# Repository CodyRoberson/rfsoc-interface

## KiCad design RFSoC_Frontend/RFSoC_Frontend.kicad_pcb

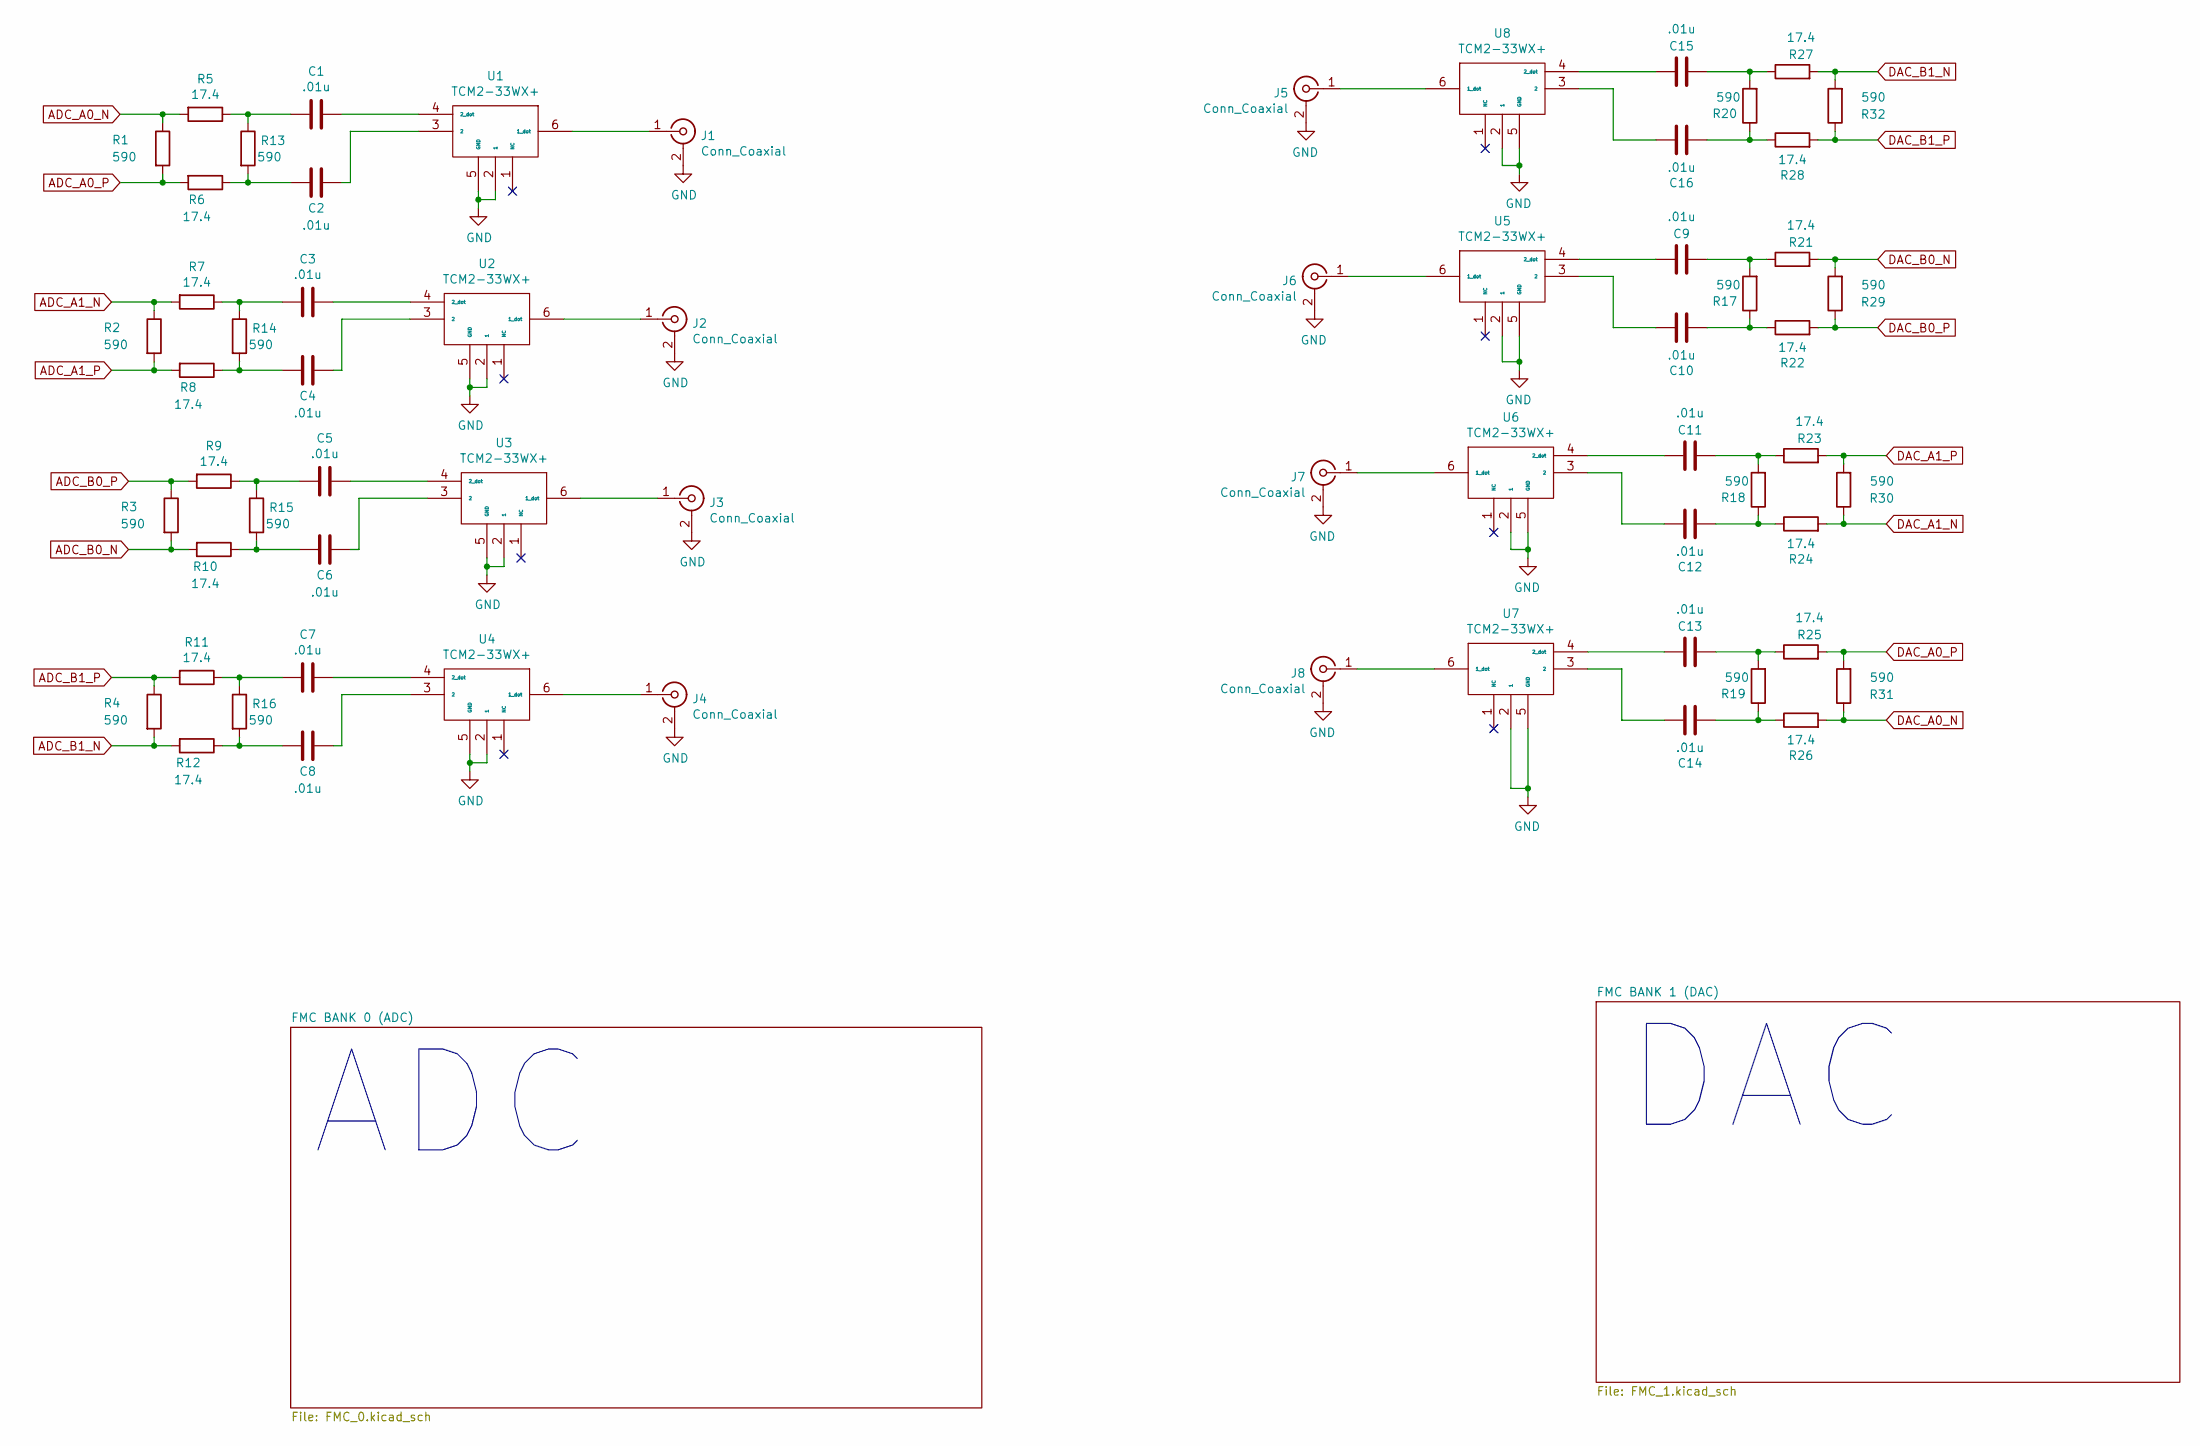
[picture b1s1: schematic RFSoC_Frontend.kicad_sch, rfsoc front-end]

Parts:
C1, C2, C3, C4, C5, C6, C7, C8, C9, C10, C11, C12, C13, C14, C15, C16: .01u; C_0402_1005Metric; Mouser Part Number 963-LMF105B7103KVHF
J1, J2, J3, J4, J5, J6, J7, J8: Conn_Coaxial; SMA_Amphenol_132289_EdgeMount
R1, R2, R3, R4, R13, R14, R15, R16, R17, R18, R19, R20, R29, R30, R31, R32: 590; R_0402_1005Metric; Mouser Part Number 667-ERA-2AEB5900X
R5, R6, R7, R8, R9, R10, R11, R12, R21, R22, R23, R24, R25, R26, R27, R28: 17.4; R_0402_1005Metric; Mouser Part Number 71-CRCW0402-17.4-E3
U1, U2, U3, U4, U5, U6, U7, U8: TCM2-33WX+; XFMR_TCM2-33WX+; Mouser Part Number 139-TCM2-33WX

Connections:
ADC_A0_N: R1.1, R5.2; also elsewhere on the board
ADC_A0_P: R1.2, R6.2; also elsewhere on the board
ADC_A1_N: R2.1, R7.2; also elsewhere on the board
ADC_A1_P: R2.2, R8.2; also elsewhere on the board
ADC_B0_N: R3.2, R10.2; also elsewhere on the board
ADC_B0_P: R3.1, R9.2; also elsewhere on the board
ADC_B1_N: R4.2, R12.2; also elsewhere on the board
ADC_B1_P: R4.1, R11.2; also elsewhere on the board
DAC_A0_N: R26.2, R31.1; also elsewhere on the board
DAC_A0_P: R25.2, R31.2; also elsewhere on the board
DAC_A1_N: R24.2, R30.1; also elsewhere on the board
DAC_A1_P: R23.2, R30.2; also elsewhere on the board
DAC_B0_N: R21.2, R29.2; also elsewhere on the board
DAC_B0_P: R22.2, R29.1; also elsewhere on the board
DAC_B1_N: R27.2, R32.2; also elsewhere on the board
DAC_B1_P: R28.2, R32.1; also elsewhere on the board
GND: J1.2 (Ext), J2.2 (Ext), J3.2 (Ext), J4.2 (Ext), J5.2 (Ext), J6.2 (Ext), J7.2 (Ext), J8.2 (Ext), U1.2 (1), U1.5 (GND), U2.2 (1), U2.5 (GND), U3.2 (1), U3.5 (GND), U4.2 (1), U4.5 (GND), U5.2 (1), U5.5 (GND), U6.2 (1), U6.5 (GND), U7.2 (1), U7.5 (GND), U8.2 (1), U8.5 (GND); also elsewhere on the board
unnamed: C1.1, U1.4 (2_dot)
unnamed: C1.2, R5.1, R13.1
unnamed: C2.1, U1.3 (2)
unnamed: C2.2, R6.1, R13.2
unnamed: C3.1, U2.4 (2_dot)
unnamed: C3.2, R7.1, R14.1
unnamed: C4.1, U2.3 (2)
unnamed: C4.2, R8.1, R14.2
unnamed: C5.1, U3.4 (2_dot)
unnamed: C5.2, R9.1, R15.1
unnamed: C6.1, U3.3 (2)
unnamed: C6.2, R10.1, R15.2
unnamed: C7.1, U4.4 (2_dot)
unnamed: C7.2, R11.1, R16.1
unnamed: C8.1, U4.3 (2)
unnamed: C8.2, R12.1, R16.2
unnamed: C9.1, U5.4 (2_dot)
unnamed: C9.2, R17.2, R21.1
unnamed: C10.1, U5.3 (2)
unnamed: C10.2, R17.1, R22.1
unnamed: C11.1, U6.4 (2_dot)
unnamed: C11.2, R18.2, R23.1
unnamed: C12.1, U6.3 (2)
unnamed: C12.2, R18.1, R24.1
unnamed: C13.1, U7.4 (2_dot)
unnamed: C13.2, R19.2, R25.1
unnamed: C14.1, U7.3 (2)
unnamed: C14.2, R19.1, R26.1
unnamed: C15.1, U8.4 (2_dot)
unnamed: C15.2, R20.2, R27.1
unnamed: C16.1, U8.3 (2)
unnamed: C16.2, R20.1, R28.1
unnamed: J1.1 (In), U1.6 (1_dot)
unnamed: J2.1 (In), U2.6 (1_dot)
unnamed: J3.1 (In), U3.6 (1_dot)
unnamed: J4.1 (In), U4.6 (1_dot)
unnamed: J5.1 (In), U8.6 (1_dot)
unnamed: J6.1 (In), U5.6 (1_dot)
unnamed: J7.1 (In), U6.6 (1_dot)
unnamed: J8.1 (In), U7.6 (1_dot)

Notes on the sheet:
ADC
DAC

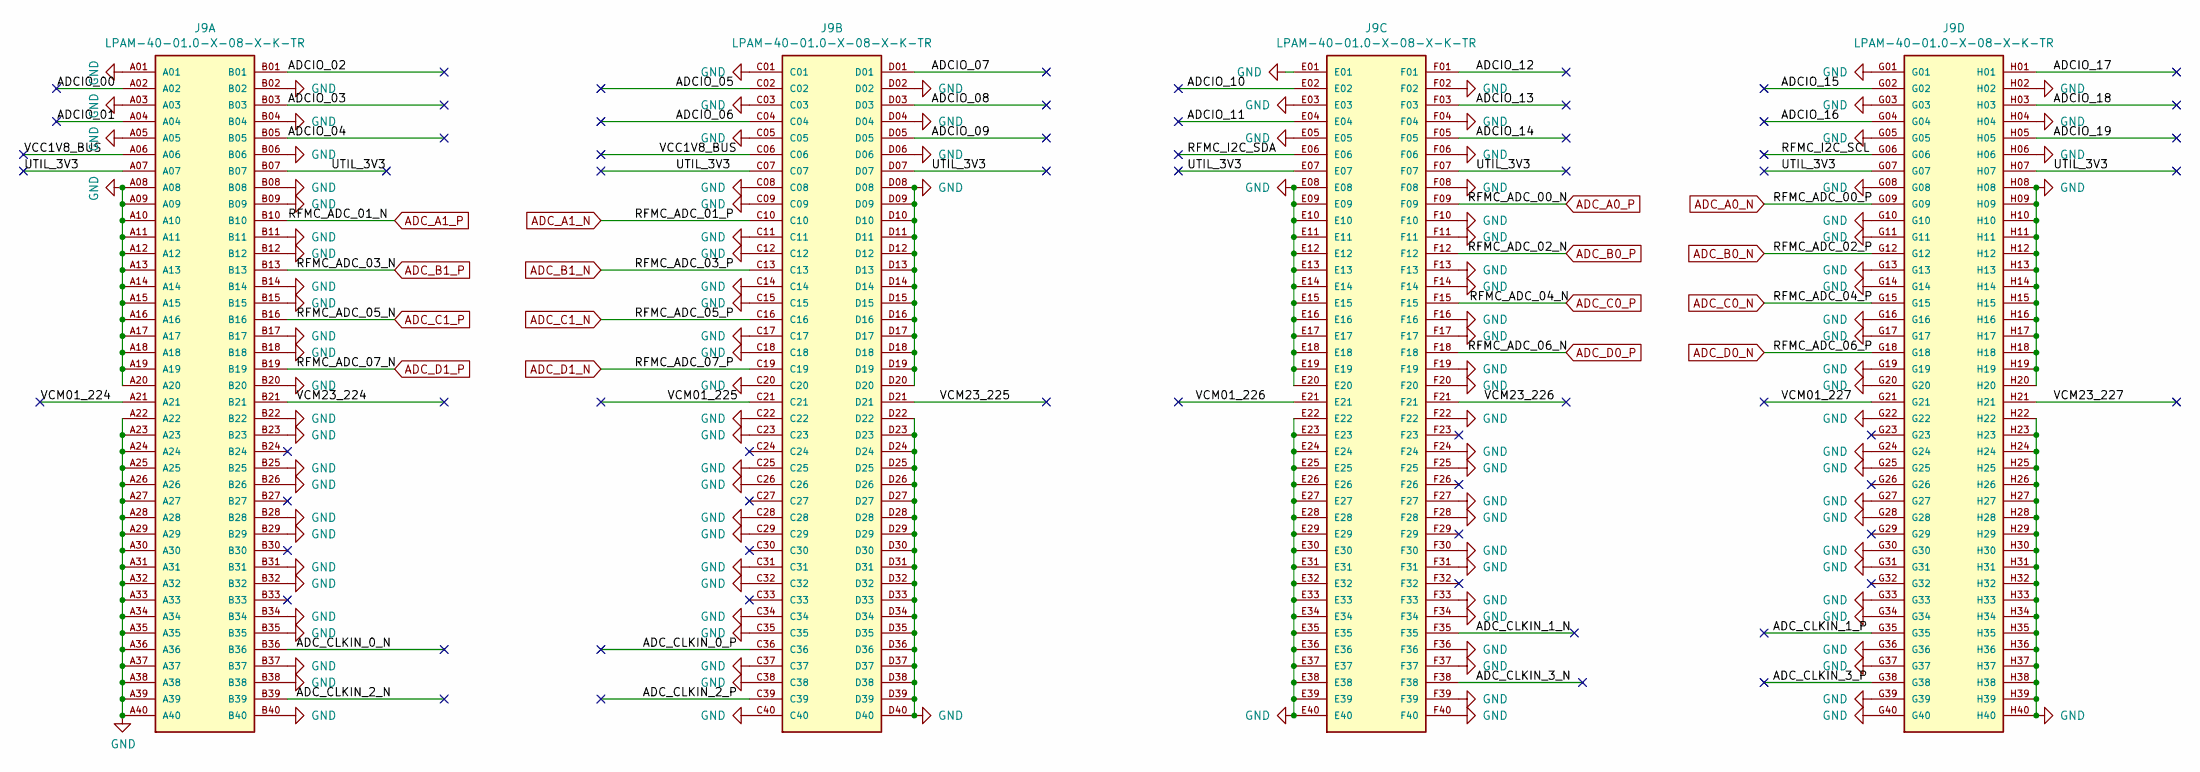
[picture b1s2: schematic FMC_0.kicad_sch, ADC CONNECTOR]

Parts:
J9: LPAM-40-01.0-X-08-X-K-TR; SAMTEC_LPAM-40-01.0-X-08-X-K-TR; PARTREV E

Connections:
/FMC BANK 0 (ADC)/ADCIO_00: J9.A02
/FMC BANK 0 (ADC)/ADCIO_01: J9.A04
/FMC BANK 0 (ADC)/ADCIO_02: J9.B01
/FMC BANK 0 (ADC)/ADCIO_03: J9.B03
/FMC BANK 0 (ADC)/ADCIO_04: J9.B05
/FMC BANK 0 (ADC)/ADCIO_05: J9.C02
/FMC BANK 0 (ADC)/ADCIO_06: J9.C04
/FMC BANK 0 (ADC)/ADCIO_07: J9.D01
/FMC BANK 0 (ADC)/ADCIO_08: J9.D03
/FMC BANK 0 (ADC)/ADCIO_09: J9.D05
/FMC BANK 0 (ADC)/ADCIO_10: J9.E02
/FMC BANK 0 (ADC)/ADCIO_11: J9.E04
/FMC BANK 0 (ADC)/ADCIO_12: J9.F01
/FMC BANK 0 (ADC)/ADCIO_13: J9.F03
/FMC BANK 0 (ADC)/ADCIO_14: J9.F05
/FMC BANK 0 (ADC)/ADCIO_15: J9.G02
/FMC BANK 0 (ADC)/ADCIO_16: J9.G04
/FMC BANK 0 (ADC)/ADCIO_17: J9.H01
/FMC BANK 0 (ADC)/ADCIO_18: J9.H03
/FMC BANK 0 (ADC)/ADCIO_19: J9.H05
/FMC BANK 0 (ADC)/ADC_CLKIN_0_N: J9.B36
/FMC BANK 0 (ADC)/ADC_CLKIN_0_P: J9.C36
/FMC BANK 0 (ADC)/ADC_CLKIN_1_N: J9.F35
/FMC BANK 0 (ADC)/ADC_CLKIN_1_P: J9.G35
/FMC BANK 0 (ADC)/ADC_CLKIN_2_N: J9.B39
/FMC BANK 0 (ADC)/ADC_CLKIN_2_P: J9.C39
/FMC BANK 0 (ADC)/ADC_CLKIN_3_N: J9.F38
/FMC BANK 0 (ADC)/ADC_CLKIN_3_P: J9.G38
/FMC BANK 0 (ADC)/RFMC_I2C_SCL: J9.G06
/FMC BANK 0 (ADC)/RFMC_I2C_SDA: J9.E06
/FMC BANK 0 (ADC)/UTIL_3V3: J9.A07, J9.B07, J9.C07, J9.D07, J9.E07, J9.F07, J9.G07, J9.H07
/FMC BANK 0 (ADC)/VCC1V8_BUS: J9.A06, J9.C06
/FMC BANK 0 (ADC)/VCM01_224: J9.A21
/FMC BANK 0 (ADC)/VCM01_225: J9.C21
/FMC BANK 0 (ADC)/VCM01_226: J9.E21
/FMC BANK 0 (ADC)/VCM01_227: J9.G21
/FMC BANK 0 (ADC)/VCM23_224: J9.B21
/FMC BANK 0 (ADC)/VCM23_225: J9.D21
/FMC BANK 0 (ADC)/VCM23_226: J9.F21
/FMC BANK 0 (ADC)/VCM23_227: J9.H21
ADC_A0_N: J9.G09; also elsewhere on the board
ADC_A0_P: J9.F09; also elsewhere on the board
ADC_A1_N: J9.C10; also elsewhere on the board
ADC_A1_P: J9.B10; also elsewhere on the board
ADC_B0_N: J9.G12; also elsewhere on the board
ADC_B0_P: J9.F12; also elsewhere on the board
ADC_B1_N: J9.C13; also elsewhere on the board
ADC_B1_P: J9.B13; also elsewhere on the board
ADC_C0_N: J9.G15
ADC_C0_P: J9.F15
ADC_C1_N: J9.C16
ADC_C1_P: J9.B16
ADC_D0_N: J9.G18
ADC_D0_P: J9.F18
ADC_D1_N: J9.C19
ADC_D1_P: J9.B19
GND: J9.A01, J9.A03, J9.A05, J9.A08, J9.A09, J9.A10, J9.A11, J9.A12, J9.A13, J9.A14, J9.A15, J9.A16, J9.A17, J9.A18, J9.A19, J9.A20, J9.A22, J9.A23, J9.A24, J9.A25, J9.A26, J9.A27, J9.A28, J9.A29, J9.A30, J9.A31, J9.A32, J9.A33, J9.A34, J9.A35, J9.A36, J9.A37, J9.A38, J9.A39, J9.A40, J9.B02, J9.B04, J9.B06, J9.B08, J9.B09, J9.B11, J9.B12, J9.B14, J9.B15, J9.B17, J9.B18, J9.B20, J9.B22, J9.B23, J9.B25, J9.B26, J9.B28, J9.B29, J9.B31, J9.B32, J9.B34, J9.B35, J9.B37, J9.B38, J9.B40, J9.C01, J9.C03, J9.C05, J9.C08, J9.C09, J9.C11, J9.C12, J9.C14, J9.C15, J9.C17, J9.C18, J9.C20, J9.C22, J9.C23, J9.C25, J9.C26, J9.C28, J9.C29, J9.C31, J9.C32, J9.C34, J9.C35, J9.C37, J9.C38, J9.C40, J9.D02, J9.D04, J9.D06, J9.D08, J9.D09, J9.D10, J9.D11, J9.D12, J9.D13, J9.D14, J9.D15, J9.D16, J9.D17, J9.D18, J9.D19, J9.D20, J9.D22, J9.D23, J9.D24, J9.D25, J9.D26, J9.D27, J9.D28, J9.D29, J9.D30, J9.D31, J9.D32, J9.D33, J9.D34, J9.D35, J9.D36, J9.D37, J9.D38, J9.D39, J9.D40, J9.E01, J9.E03, J9.E05, J9.E08, J9.E09, J9.E10, J9.E11, J9.E12, J9.E13, J9.E14, J9.E15, J9.E16, J9.E17, J9.E18, J9.E19, J9.E20, J9.E22, J9.E23, J9.E24, J9.E25, J9.E26, J9.E27, J9.E28, J9.E29, J9.E30, J9.E31, J9.E32, J9.E33, J9.E34, J9.E35, J9.E36, J9.E37, J9.E38, J9.E39, J9.E40, J9.F02, J9.F04, J9.F06, J9.F08, J9.F10, J9.F11, J9.F13, J9.F14, J9.F16, J9.F17, J9.F19, J9.F20, J9.F22, J9.F24, J9.F25, J9.F27, J9.F28, J9.F30, J9.F31, J9.F33, J9.F34, J9.F36, J9.F37, J9.F39, J9.F40, J9.G01, J9.G03, J9.G05, J9.G08, J9.G10, J9.G11, J9.G13, J9.G14, J9.G16, J9.G17, J9.G19, J9.G20, J9.G22, J9.G24, J9.G25, J9.G27, J9.G28, J9.G30, J9.G31, J9.G33, J9.G34, J9.G36, J9.G37, J9.G39, J9.G40, J9.H02, J9.H04, J9.H06, J9.H08, J9.H09, J9.H10, J9.H11, J9.H12, J9.H13, J9.H14, J9.H15, J9.H16, J9.H17, J9.H18, J9.H19, J9.H20, J9.H22, J9.H23, J9.H24, J9.H25, J9.H26, J9.H27, J9.H28, J9.H29, J9.H30, J9.H31, J9.H32, J9.H33, J9.H34, J9.H35, J9.H36, J9.H37, J9.H38, J9.H39, J9.H40; also elsewhere on the board

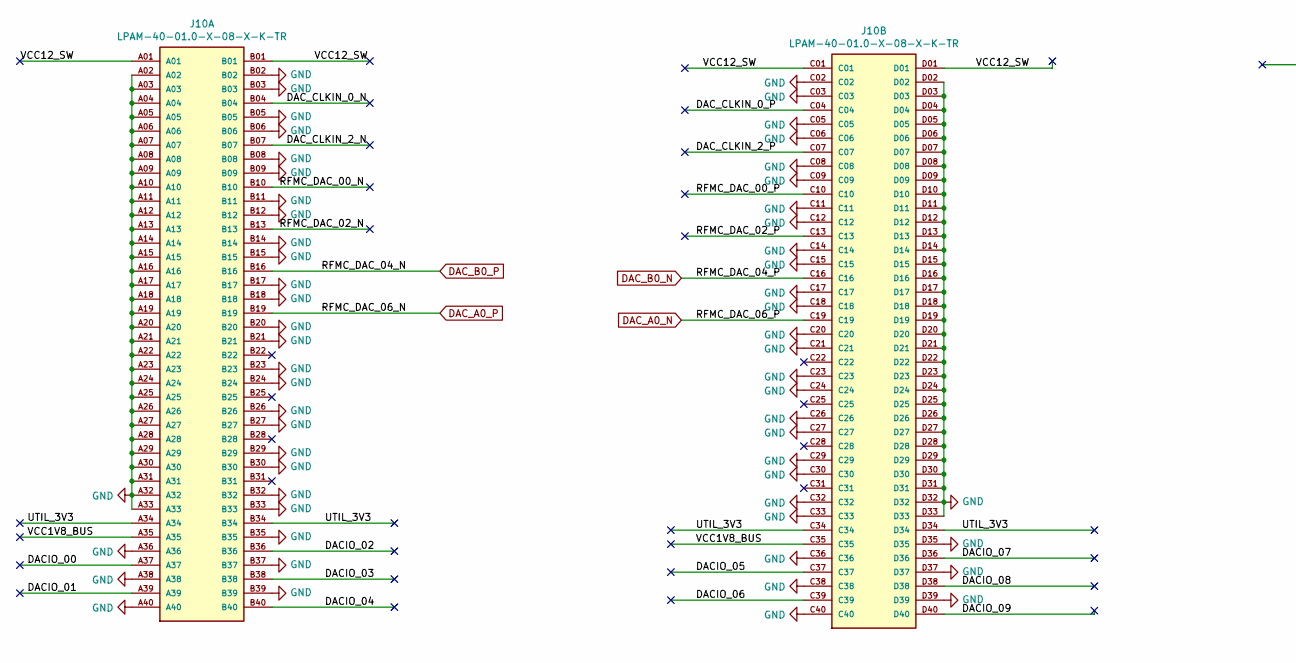
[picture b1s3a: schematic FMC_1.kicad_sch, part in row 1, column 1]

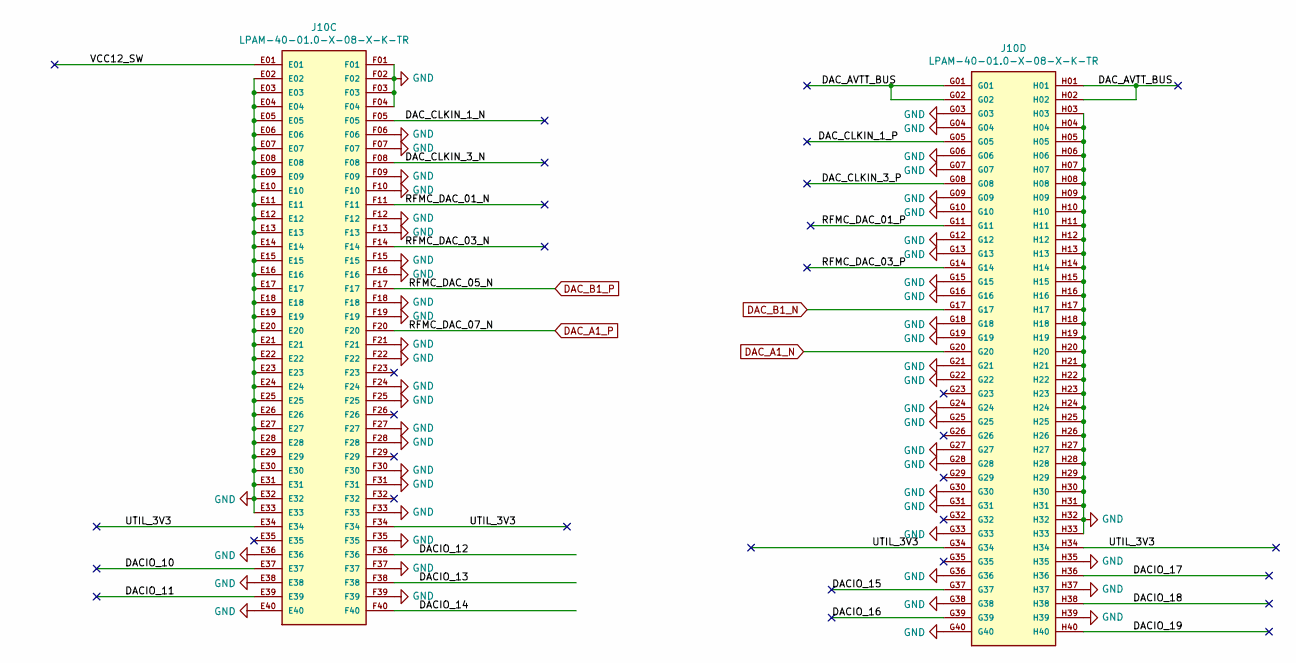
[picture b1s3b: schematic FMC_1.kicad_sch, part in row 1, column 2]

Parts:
J10: LPAM-40-01.0-X-08-X-K-TR; SAMTEC_LPAM-40-01.0-X-08-X-K-TR; PARTREV E

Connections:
/FMC BANK 1 (DAC)/DACIO_00: J10.A37
/FMC BANK 1 (DAC)/DACIO_01: J10.A39
/FMC BANK 1 (DAC)/DACIO_02: J10.B36
/FMC BANK 1 (DAC)/DACIO_03: J10.B38
/FMC BANK 1 (DAC)/DACIO_04: J10.B40
/FMC BANK 1 (DAC)/DACIO_05: J10.C37
/FMC BANK 1 (DAC)/DACIO_06: J10.C39
/FMC BANK 1 (DAC)/DACIO_07: J10.D36
/FMC BANK 1 (DAC)/DACIO_08: J10.D38
/FMC BANK 1 (DAC)/DACIO_09: J10.D40
/FMC BANK 1 (DAC)/DACIO_10: J10.E37
/FMC BANK 1 (DAC)/DACIO_11: J10.E39
/FMC BANK 1 (DAC)/DACIO_12: J10.F36
/FMC BANK 1 (DAC)/DACIO_13: J10.F38
/FMC BANK 1 (DAC)/DACIO_14: J10.F40
/FMC BANK 1 (DAC)/DACIO_15: J10.G37
/FMC BANK 1 (DAC)/DACIO_16: J10.G39
/FMC BANK 1 (DAC)/DACIO_17: J10.H36
/FMC BANK 1 (DAC)/DACIO_18: J10.H38
/FMC BANK 1 (DAC)/DACIO_19: J10.H40
/FMC BANK 1 (DAC)/DAC_AVTT_BUS: J10.G01, J10.G02, J10.H01, J10.H02
/FMC BANK 1 (DAC)/DAC_CLKIN_0_N: J10.B04
/FMC BANK 1 (DAC)/DAC_CLKIN_0_P: J10.C04
/FMC BANK 1 (DAC)/DAC_CLKIN_1_N: J10.F05
/FMC BANK 1 (DAC)/DAC_CLKIN_1_P: J10.G05
/FMC BANK 1 (DAC)/DAC_CLKIN_2_N: J10.B07
/FMC BANK 1 (DAC)/DAC_CLKIN_2_P: J10.C07
/FMC BANK 1 (DAC)/DAC_CLKIN_3_N: J10.F08
/FMC BANK 1 (DAC)/DAC_CLKIN_3_P: J10.G08
/FMC BANK 1 (DAC)/RFMC_DAC_00_N: J10.B10
/FMC BANK 1 (DAC)/RFMC_DAC_00_P: J10.C10
/FMC BANK 1 (DAC)/RFMC_DAC_01_N: J10.F11
/FMC BANK 1 (DAC)/RFMC_DAC_01_P: J10.G11
/FMC BANK 1 (DAC)/RFMC_DAC_02_N: J10.B13
/FMC BANK 1 (DAC)/RFMC_DAC_02_P: J10.C13
/FMC BANK 1 (DAC)/RFMC_DAC_03_N: J10.F14
/FMC BANK 1 (DAC)/RFMC_DAC_03_P: J10.G14
/FMC BANK 1 (DAC)/UTIL_3V3: J10.A34, J10.B34, J10.C34, J10.D34, J10.E34, J10.F34, J10.G34, J10.H34
/FMC BANK 1 (DAC)/VCC1V8_BUS: J10.A35, J10.C35
/FMC BANK 1 (DAC)/VCC12_SW: J10.A01, J10.B01, J10.C01, J10.D01, J10.E01
DAC_A0_N: J10.C19; also elsewhere on the board
DAC_A0_P: J10.B19; also elsewhere on the board
DAC_A1_N: J10.G20; also elsewhere on the board
DAC_A1_P: J10.F20; also elsewhere on the board
DAC_B0_N: J10.C16; also elsewhere on the board
DAC_B0_P: J10.B16; also elsewhere on the board
DAC_B1_N: J10.G17; also elsewhere on the board
DAC_B1_P: J10.F17; also elsewhere on the board
GND: J10.A02, J10.A03, J10.A04, J10.A05, J10.A06, J10.A07, J10.A08, J10.A09, J10.A10, J10.A11, J10.A12, J10.A13, J10.A14, J10.A15, J10.A16, J10.A17, J10.A18, J10.A19, J10.A20, J10.A21, J10.A22, J10.A23, J10.A24, J10.A25, J10.A26, J10.A27, J10.A28, J10.A29, J10.A30, J10.A31, J10.A32, J10.A33, J10.A36, J10.A38, J10.A40, J10.B02, J10.B03, J10.B05, J10.B06, J10.B08, J10.B09, J10.B11, J10.B12, J10.B14, J10.B15, J10.B17, J10.B18, J10.B20, J10.B21, J10.B23, J10.B24, J10.B26, J10.B27, J10.B29, J10.B30, J10.B32, J10.B33, J10.B35, J10.B37, J10.B39, J10.C02, J10.C03, J10.C05, J10.C06, J10.C08, J10.C09, J10.C11, J10.C12, J10.C14, J10.C15, J10.C17, J10.C18, J10.C20, J10.C21, J10.C23, J10.C24, J10.C26, J10.C27, J10.C29, J10.C30, J10.C32, J10.C33, J10.C36, J10.C38, J10.C40, J10.D02, J10.D03, J10.D04, J10.D05, J10.D06, J10.D07, J10.D08, J10.D09, J10.D10, J10.D11, J10.D12, J10.D13, J10.D14, J10.D15, J10.D16, J10.D17, J10.D18, J10.D19, J10.D20, J10.D21, J10.D22, J10.D23, J10.D24, J10.D25, J10.D26, J10.D27, J10.D28, J10.D29, J10.D30, J10.D31, J10.D32, J10.D33, J10.D35, J10.D37, J10.D39, J10.E02, J10.E03, J10.E04, J10.E05, J10.E06, J10.E07, J10.E08, J10.E09, J10.E10, J10.E11, J10.E12, J10.E13, J10.E14, J10.E15, J10.E16, J10.E17, J10.E18, J10.E19, J10.E20, J10.E21, J10.E22, J10.E23, J10.E24, J10.E25, J10.E26, J10.E27, J10.E28, J10.E29, J10.E30, J10.E31, J10.E32, J10.E33, J10.E36, J10.E38, J10.E40, J10.F01, J10.F02, J10.F03, J10.F04, J10.F06, J10.F07, J10.F09, J10.F10, J10.F12, J10.F13, J10.F15, J10.F16, J10.F18, J10.F19, J10.F21, J10.F22, J10.F24, J10.F25, J10.F27, J10.F28, J10.F30, J10.F31, J10.F33, J10.F35, J10.F37, J10.F39, J10.G03, J10.G04, J10.G06, J10.G07, J10.G09, J10.G10, J10.G12, J10.G13, J10.G15, J10.G16, J10.G18, J10.G19, J10.G21, J10.G22, J10.G24, J10.G25, J10.G27, J10.G28, J10.G30, J10.G31, J10.G33, J10.G36, J10.G38, J10.G40, J10.H03, J10.H04, J10.H05, J10.H06, J10.H07, J10.H08, J10.H09, J10.H10, J10.H11, J10.H12, J10.H13, J10.H14, J10.H15, J10.H16, J10.H17, J10.H18, J10.H19, J10.H20, J10.H21, J10.H22, J10.H23, J10.H24, J10.H25, J10.H26, J10.H27, J10.H28, J10.H29, J10.H30, J10.H31, J10.H32, J10.H33, J10.H35, J10.H37, J10.H39; also elsewhere on the board

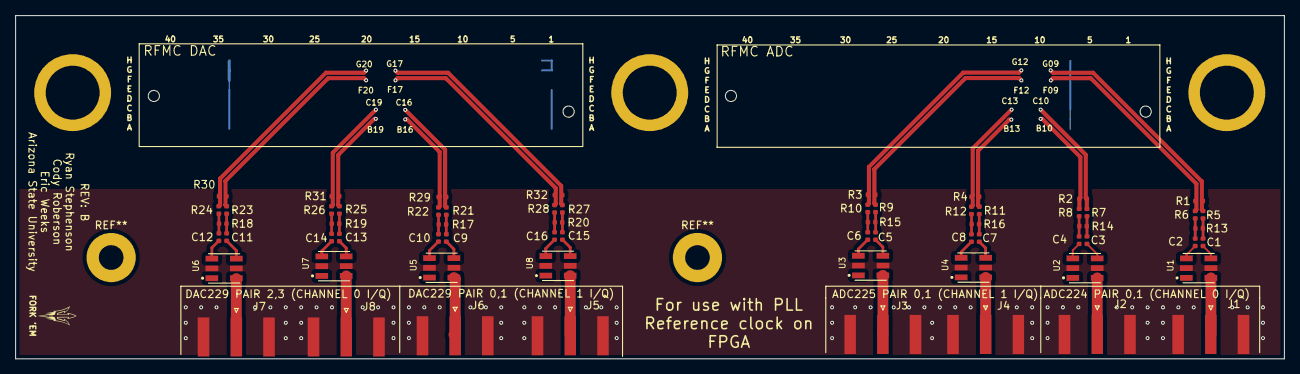
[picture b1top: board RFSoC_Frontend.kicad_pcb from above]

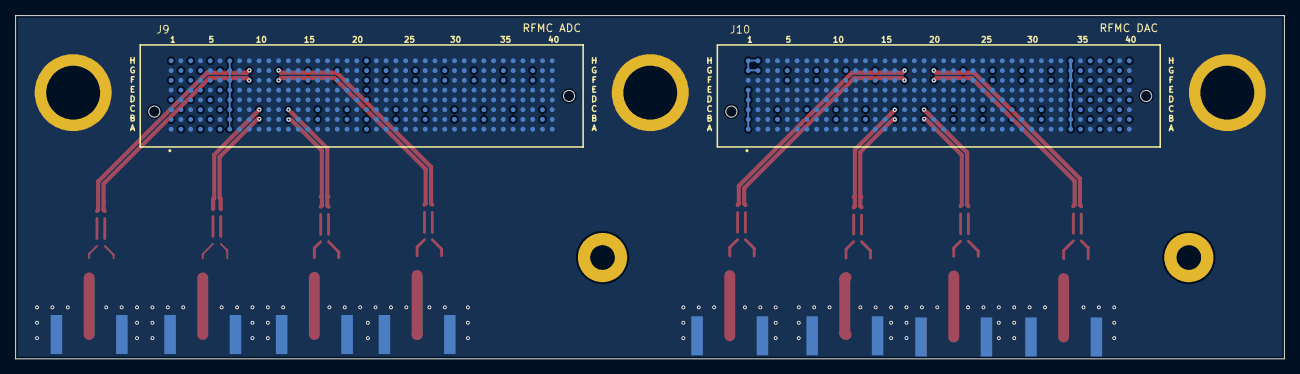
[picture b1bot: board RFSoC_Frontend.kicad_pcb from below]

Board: 2 copper layers, 164.9 x 44.6 mm, 69 parts (2 on the bottom side), 63 nets.

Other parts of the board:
e, e1, e2: MountingHole_2.2mm_M2_DIN965_Pad

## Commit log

2022-05-05 Transferred Files from Erics Folder
2022-05-05 added labels
2022-07-05 current
2022-07-05 updated to remove 'eyeballed' measurements
2022-07-14 updates
    updated 3d footprints
2022-08-19 updated design for fixes
2022-08-24 yes?
2022-09-16 fixed grounded util 3v3 pins on the LPAM Cnctr
    updated to REV B
